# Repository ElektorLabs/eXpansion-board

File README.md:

# Elektor eXpansion Board v1.01 🚀

Welcome to the GitHub repository for the Elektor eXpansion Board v1.01! This repository contains all the necessary files and documentation for the expansion board designed for Seeed Studio XIAO microcontroller boards.

## What's New in v1.01? ✨
### 🛠️ Improved PCB Layout for Better Performance
We've fine-tuned the overall PCB design to boost both performance and usability.

### 🔗 Enhanced XIAO Board Footprint
Now supports both SMD and THT soldering for greater flexibility in your projects.

### ⚡ Optimized Track Routing
Power, I2C, and UART tracks have been optimized to deliver better signal integrity.

### 🎛️ Improved Button and LED Placement
Enjoy easier accessibility with a more user-friendly layout.

## Overview 🌟

The Elektor eXpansion Board v1.0 is designed to enhance the functionality and connectivity of the Seeed Studio XIAO microcontroller lineup, including models like the SMD21, ESP32C3, C6, ESP32S3, and more. This board features multiple connectors and robust protection features, making it ideal for a wide range of applications, from prototyping and educational projects to IoT solutions and field applications.

## Features ✨

- **Multiple Connectivity Options**:
  - 4 Grove I2C connectors 🔌
  - 2 Qwiic connectors 🔌
  - UART output with switchable RX and TX pins via jumpers 🛠️

- **Power Management**:
  - Screw terminal connector for 3V, 5V, and ground ⚡
  - 2mm pitch connector for batteries 🔋

- **Additional Features**:
  - Button and LED for basic input/output functionality 💡
  - ESD protection on 3V, 5V, I2C, and SPI lines to prevent damage from electrostatic discharge 🛡️

## Repository Structure 🗂️

- **hardware**:
  - **elektor-eXpansion-board-V1-0**:
    - **production**: Contains production and Gerber files for the expansion board 🏭
    - **kicad_files**: Contains the KiCad project files for the expansion board 📁

## Getting Started 🛠️

To get started with the Elektor eXpansion Board v1.0, you can clone this repository and open the KiCad project files found in the `hardware/elektor-eXpansion-board-V1-0/kicad_files` directory. The production and Gerber files required for manufacturing the board are located in the `hardware/elektor-eXpansion-board-V1-0/production` directory.

### Cloning the Repository 📥

```bash
git clone https://github.com/elektorLabs/elektor-eXpansion-board-v1.0.git
```

### Opening the Project in KiCad 💻

1. Open KiCad.
2. Navigate to the cloned repository folder.
3. Open the KiCad project file located in `hardware/elektor-eXpansion-board-V1-0/`.

### Manufacturing the Board 🏭

To manufacture the Elektor eXpansion Board v1.0, use the Gerber files located in the `hardware/elektor-eXpansion-board-V1-0/production` directory. These files can be uploaded to any PCB manufacturing service.

## Contribution 🤝

Contributions to this project are welcome! If you have any suggestions, improvements, or bug fixes, please submit a pull request or open an issue.

## License 📜

This project is licensed under the CC BY-NC 4.0 LEGAL CODE - Attribution-NonCommercial 4.0 International. See the [LICENSE](https://creativecommons.org/licenses/by-nc/4.0/legalcode.en) file for more details.

## Contact 📧

If you have any questions or need further assistance, feel free to open an issue on this repository or contact the project maintainer.

Happy tinkering! 🛠️✨

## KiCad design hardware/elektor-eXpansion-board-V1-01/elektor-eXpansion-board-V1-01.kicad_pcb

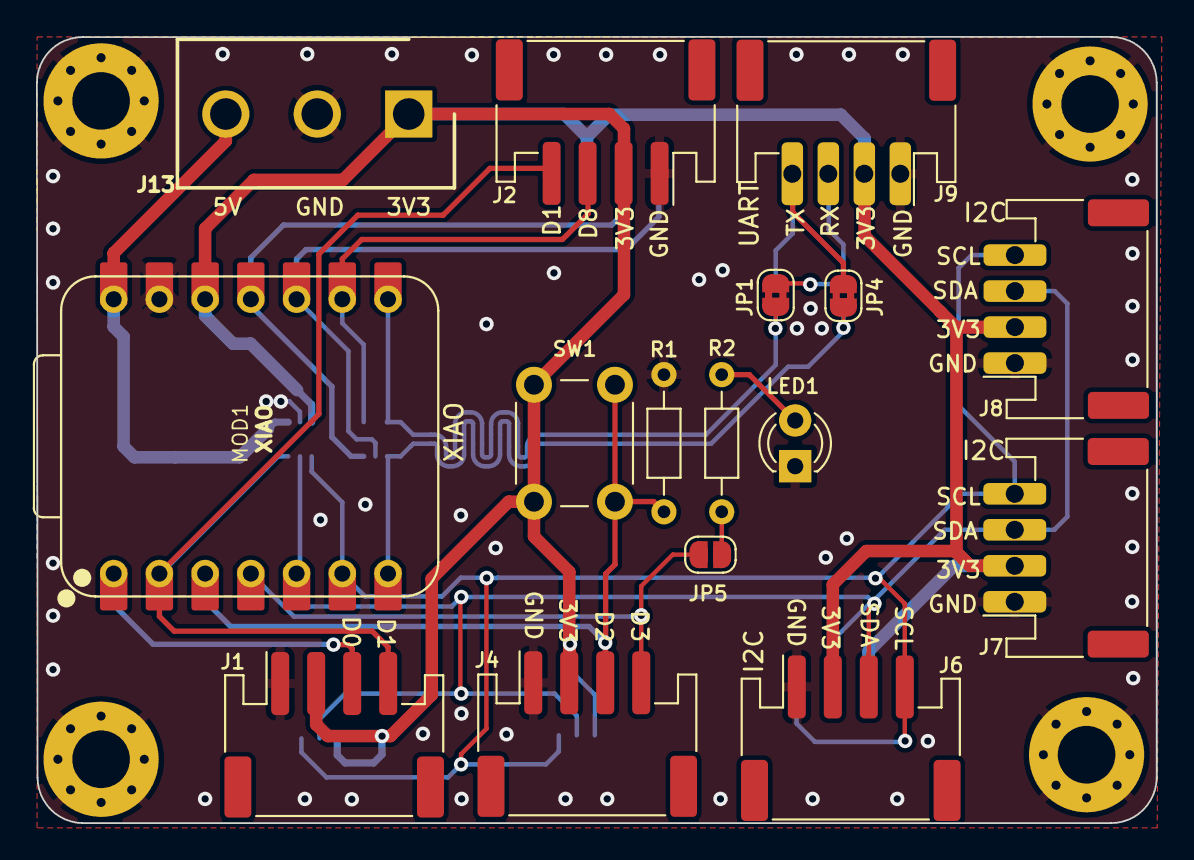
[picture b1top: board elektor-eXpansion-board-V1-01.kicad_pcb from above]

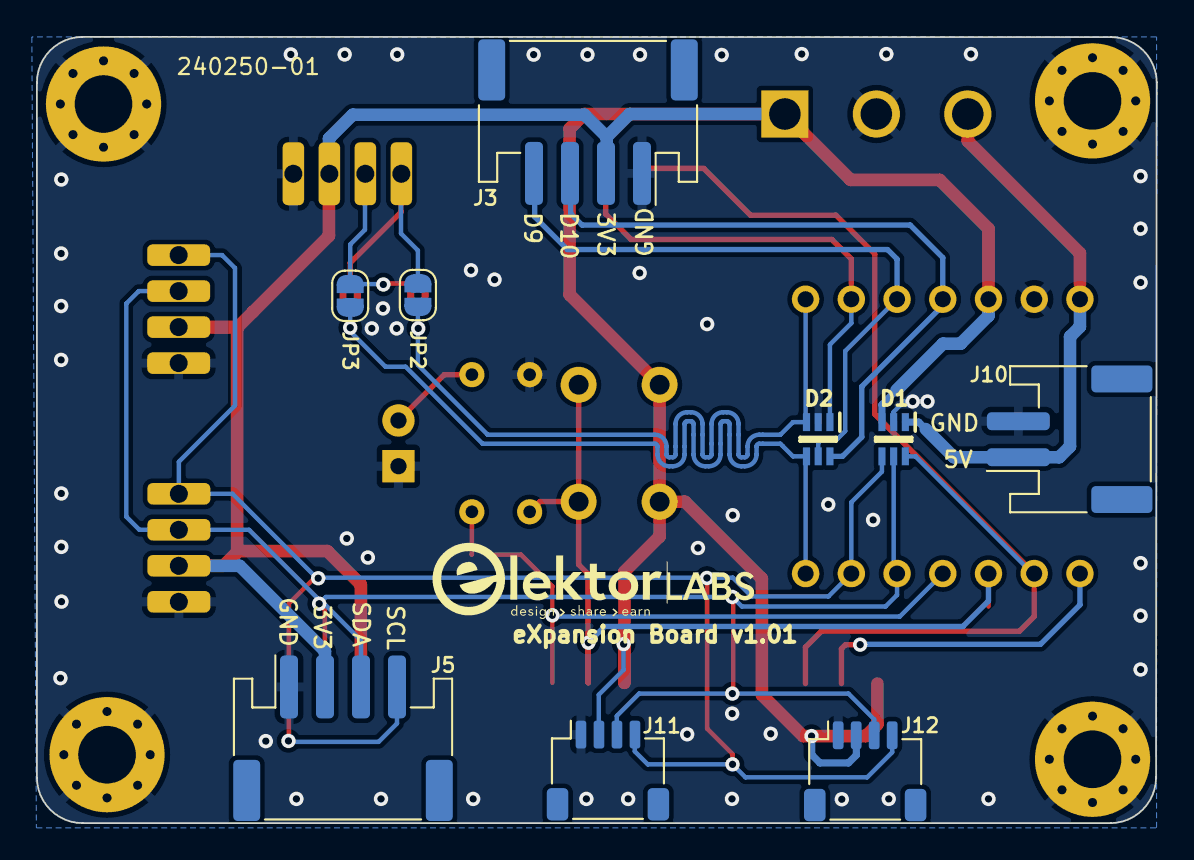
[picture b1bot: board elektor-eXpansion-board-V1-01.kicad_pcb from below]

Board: 2 copper layers, 62.2 x 43.7 mm, 29 parts (9 on the bottom side), 18 nets.

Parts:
D1, D2: SMF05C.TCT; SOT65P210X110-6N
H1, H2, H3, H4: MountingHole_Pad; MountingHole_3.2mm_M3_Pad_Via
J1: IO1; JST_PH_S4B-PH-SM4-TB_1x04-1MP_P2.00mm_Horizontal
J2: IO3; JST_PH_S4B-PH-SM4-TB_1x04-1MP_P2.00mm_Horizontal
J3: IO4; JST_PH_S4B-PH-SM4-TB_1x04-1MP_P2.00mm_Horizontal
J4: IO2; JST_PH_S4B-PH-SM4-TB_1x04-1MP_P2.00mm_Horizontal
J5: I2C..; JST_PH_S4B-PH-SM4-TB_1x04-1MP_P2.00mm_Horizontal
J6, J7, J8: I2C.; JST_PH_S4B-PH-SM4-TB_1x04-1MP_P2.00mm_Horizontal
J9: UART; JST_PH_S4B-PH-SM4-TB_1x04-1MP_P2.00mm_Horizontal
J10: 5V-GND; JST_PH_S2B-PH-SM4-TB_1x02-1MP_P2.00mm_Horizontal
J11, J12: Qwiic; JST_SH_SM04B-SRSS-TB_1x04-1MP_P1.00mm_Horizontal
J13: 5442219; SHDR3W110P0X508_1X3_1524X810X1015P
JP1, JP4: Jumper_2_Bridged; SolderJumper-2_P1.3mm_Bridged2Bar_RoundedPad1.0x1.5mm
JP2, JP3, JP5: SolderJumper-2_P1.3mm_Open_RoundedPad1.0x1.5mm
LED1: LED; LED_D3.0mm
MOD1: SeeeduinoXIAO; XIAO-ESP32C3-DIP
R1: 200; R_Axial_DIN0204_L3.6mm_D1.6mm_P7.62mm_Horizontal
R2: 10k; R_Axial_DIN0204_L3.6mm_D1.6mm_P7.62mm_Horizontal
SW1: SW_Push; SW_PUSH_6mm

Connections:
+3V3: D1.3 (CATHODE_2), J1.2, J2.2, J3.2, J4.2, J5.2, J6.2, J7.2, J8.2, J9.2, J11.2, J12.2, J13.1, MOD1.12 (3V3), SW1.1
+5V: D1.1 (CATHODE_1), J10.1, J13.3, MOD1.14 (5V)
D0: J1.3, MOD1.1 (PA02_A0_D0)
D1: D1.6 (CATHODE_5), J1.4, J2.4, MOD1.2 (PA4_A1_D1)
D2: J4.3, MOD1.3 (PA10_A2_D2), R2.1, SW1.2
D3: J4.4, JP5.2 (B), MOD1.4 (PA11_A3_D3)
D8: D2.1 (CATHODE_1), J2.3, MOD1.9 (PA7_A8_D8_SCK)
D9: D2.5 (CATHODE_4), J3.4, MOD1.10 (PA5_A9_D9_MISO)
D10: D2.6 (CATHODE_5), J3.3, MOD1.11 (PA6_A10_D10_MOSI)
GND: D1.2 (COMMON_ANODE), D2.2 (COMMON_ANODE), H1.1, H2.1, H3.1, H4.1, J1.1, J2.1, J3.1, J4.1, J5.1, J6.1, J7.1, J8.1, J9.1, J10.2, J11.1, J12.1, J13.2, LED1.1 (K), MOD1.13 (GND), R2.2
unnamed: J9.3, JP1.2 (B), JP3.2 (B)
unnamed: J9.4, JP2.2 (B), JP4.2 (B)
unnamed: JP5.1 (A), R1.1
unnamed: LED1.2 (A), R1.2
SCL: D1.4 (CATHODE_3), J5.4, J6.4, J7.4, J8.4, J11.4, J12.4, MOD1.6 (PA9_A5_D5_SCL)
SDA: D1.5 (CATHODE_4), J5.3, J6.3, J7.3, J8.3, J11.3, J12.3, MOD1.5 (PA8_A4_D4_SDA)
UART_N: D2.3 (CATHODE_2), JP1.1 (A), JP2.1 (A), MOD1.8 (PB09_A7_D7_RX)
UART_P: D2.4 (CATHODE_3), JP3.1 (A), JP4.1 (A), MOD1.7 (PB08_A6_D6_TX)

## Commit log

2024-05-21 added files
2024-05-21 Create LICENSE.md
    https://creativecommons.org/licenses/by-nc/4.0/legalcode.en
2024-06-25 added enclosure files
2024-12-02 v1.01
    feat: Release v1.01 of Elektor eXpansion Board
    - Improved overall PCB layout for better performance and usability.
    - Enhanced Xiao board footprint to support both SMD and THT soldering.
    - Optimized power, I2C, and UART track routing for improved signal integrity.
    - Adjusted placement of button and LED for better accessibility.
